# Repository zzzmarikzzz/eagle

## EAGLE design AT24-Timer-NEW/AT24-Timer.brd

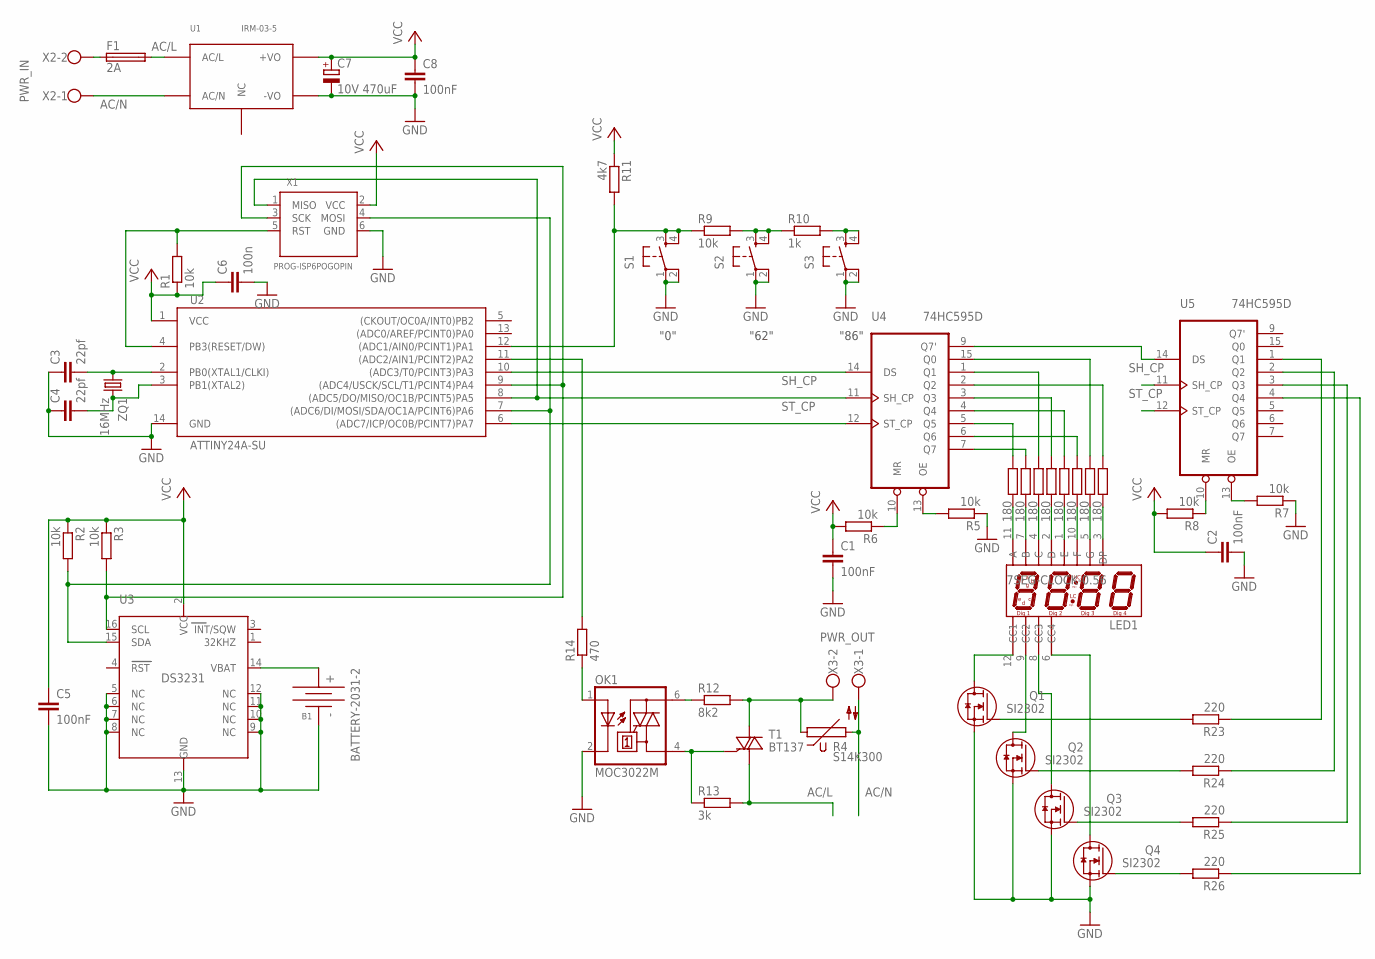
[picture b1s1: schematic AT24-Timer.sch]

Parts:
B1: BATTERY-2031-2; BTH2032-2
C1, C2, C5: 100nF; C0603
C3, C4: 22pf; C0603
C6: 100n; C0603
C7: 10V 470uF; D/7343-31W
C8: 100nF; C0805
F1: 2A; SH22,5A
LED1: 7SEG-CLOCK-0.56; 7SEG_4DIG_0.56
OK1: MOC3022M; DIL06
Q1, Q2, Q3, Q4: SI2302; SOT-23-GSD
R1, R2, R3, R5, R6, R7, R8, R9: 10k; R0805
R4: S14K300
R10: 1k; R0805
R11: 4k7; R0805
R12: 8k2; 0207/7
R13: 3k; 0207/7
R14: 470; R0805
R15, R16, R17, R18, R19, R20, R21, R22: 180; R0805
R23, R24, R25, R26: 220; R0805
S1, S2, S3: DTS-6
T1: BT137; TO220AB
U1: IRM-03-5; IRM-03-*
U2: ATTINY24A-SU; SO14
U3: DS3231; SO16L
U4, U5: 74HC595D; SO16
X1: PROG-ISP6POGOPIN; PROG_POGOPIN
X2: PWR_IN; W237-102
X3: PWR_OUT; W237-102
ZQ1: 16MHz; HC49/S

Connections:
AC/L: F1.2, R13.2, T1.1 (A1), U1.P$1 (AC/L)
AC/N: R4.2, U1.P$2 (AC/N), X2.1, X3.1
GND: B1.-, C1.2, C2.2, C3.1, C4.1, C5.2, C6.2, C7.-, C8.2, OK1.2 (C), Q1.S, Q2.S, Q3.S, Q4.S, R5.1, R7.1, S1.1, S1.2, S2.1, S2.2, S3.1, S3.2, U1.P$4 (-VO), U2.14 (GND), U3.5 (NC), U3.6 (NC), U3.7 (NC), U3.8 (NC), U3.9 (NC), U3.10 (NC), U3.11 (NC), U3.12 (NC), U3.13 (GND), U4.8 (GND), U5.8 (GND), X1.6 (GND)
unnamed: B1.+, U3.14 (VBAT)
unnamed: F1.1, X2.2
unnamed: R2.2, U2.7 ((ADC6/DI/MOSI/SDA/OC1A/PCINT6)PA6), U3.15 (SDA), X1.4 (MOSI)
unnamed: R3.2, U2.9 ((ADC4/USCK/SCL/T1/PCINT4)PA4), U3.16 (SCL), X1.3 (SCK)
unnamed: R1.2, U2.4 (PB3(RESET/DW)), X1.5 (RST)
unnamed: R9.2, R10.1, S2.3, S2.4
unnamed: C3.2, U2.2 (PB0(XTAL1/CLKI)), ZQ1.1
unnamed: C4.2, U2.3 (PB1(XTAL2)), ZQ1.2
unnamed: R6.1, U4.10 (MR)
unnamed: R9.1, R11.2, S1.3, S1.4, U2.12 ((ADC1/AIN0/PCINT1)PA1)
unnamed: OK1.6 (A2), R12.1
unnamed: R4.1, R12.2, T1.2 (A2), X3.2
unnamed: OK1.4 (A1), R13.1, T1.3 (G)
unnamed: R5.2, U4.13 (OE)
unnamed: OK1.1 (A), R14.1
unnamed: R8.1, U5.10 (MR)
unnamed: R7.2, U5.13 (OE)
unnamed: U2.10 ((ADC3/T0/PCINT3)PA3), U4.14 (DS)
unnamed: R15.1, U4.5 (Q5)
unnamed: R16.1, U4.7 (Q7)
unnamed: U4.9 (Q7'), U5.14 (DS)
unnamed: R17.1, U4.1 (Q1)
unnamed: R18.1, U4.3 (Q3)
unnamed: R19.1, U4.4 (Q4)
unnamed: R20.1, U4.6 (Q6)
unnamed: R21.1, U4.15 (Q0)
unnamed: R22.1, U4.2 (Q2)
unnamed: LED1.12 (CC1), Q1.D
unnamed: LED1.9 (CC2), Q2.D
unnamed: LED1.8 (CC3), Q3.D
unnamed: LED1.6 (CC4), Q4.D
unnamed: R23.1, U5.1 (Q1)
unnamed: R24.1, U5.2 (Q2)
unnamed: R25.1, U5.3 (Q3)
unnamed: R26.1, U5.4 (Q4)
unnamed: R10.2, S3.3, S3.4
unnamed: LED1.7 (B), R16.2
unnamed: LED1.4 (C), R17.2
unnamed: LED1.2 (D), R18.2
unnamed: LED1.1 (E), R19.2
unnamed: LED1.10 (F), R20.2
unnamed: LED1.5 (G), R21.2
unnamed: LED1.3 (DP), R22.2
unnamed: LED1.11 (A), R15.2
unnamed: Q4.G, R26.2
unnamed: Q3.G, R25.2
unnamed: Q2.G, R24.2
unnamed: Q1.G, R23.2
NC: U1.P$3 (NC)
OPTOCOUP: R14.2, U2.11 ((ADC2/AIN1/PCINT2)PA2)
SH_CP: U2.8 ((ADC5/DO/MISO/OC1B/PCINT5)PA5), U4.11 (SH_CP), U5.11 (SH_CP), X1.1 (MISO)
ST_CP: U2.6 ((ADC7/ICP/OC0B/PCINT7)PA7), U4.12 (ST_CP), U5.12 (ST_CP)
VCC: C1.1, C2.1, C5.1, C6.1, C7.+, C8.1, R1.1, R2.1, R3.1, R6.2, R8.2, R11.1, U1.P$5 (+VO), U2.1 (VCC), U3.2 (VCC), U4.16 (VCC), U5.16 (VCC), X1.2 (VCC)

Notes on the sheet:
"0"
"62"
"86"

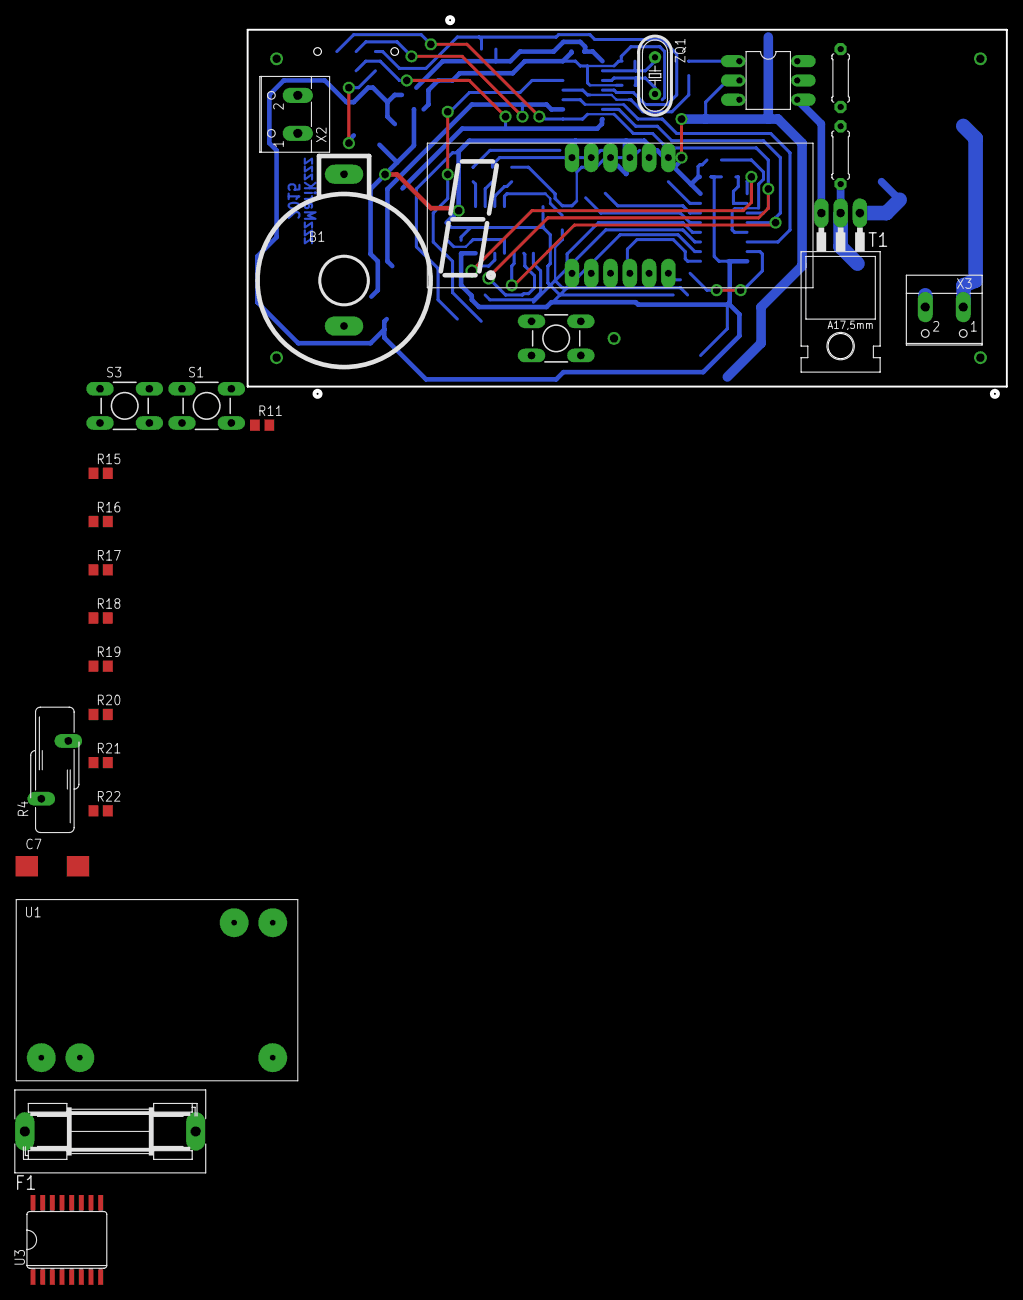
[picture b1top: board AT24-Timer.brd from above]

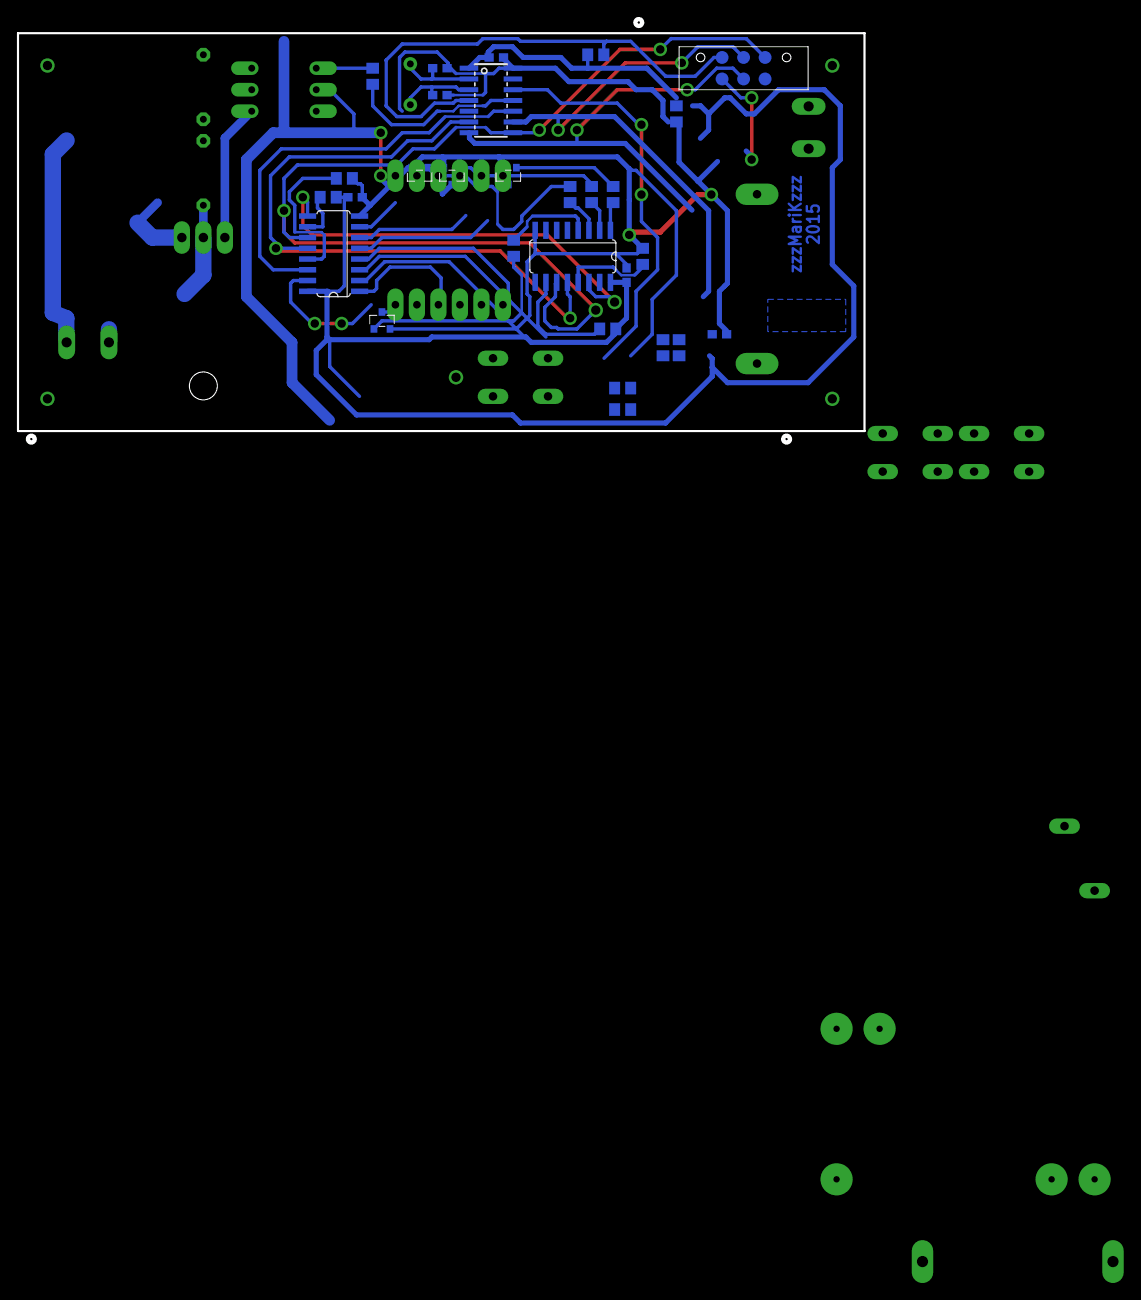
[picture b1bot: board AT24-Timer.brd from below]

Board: 2 copper layers, 100.0 x 49.7 mm, 55 parts (29 on the bottom side), 55 nets.

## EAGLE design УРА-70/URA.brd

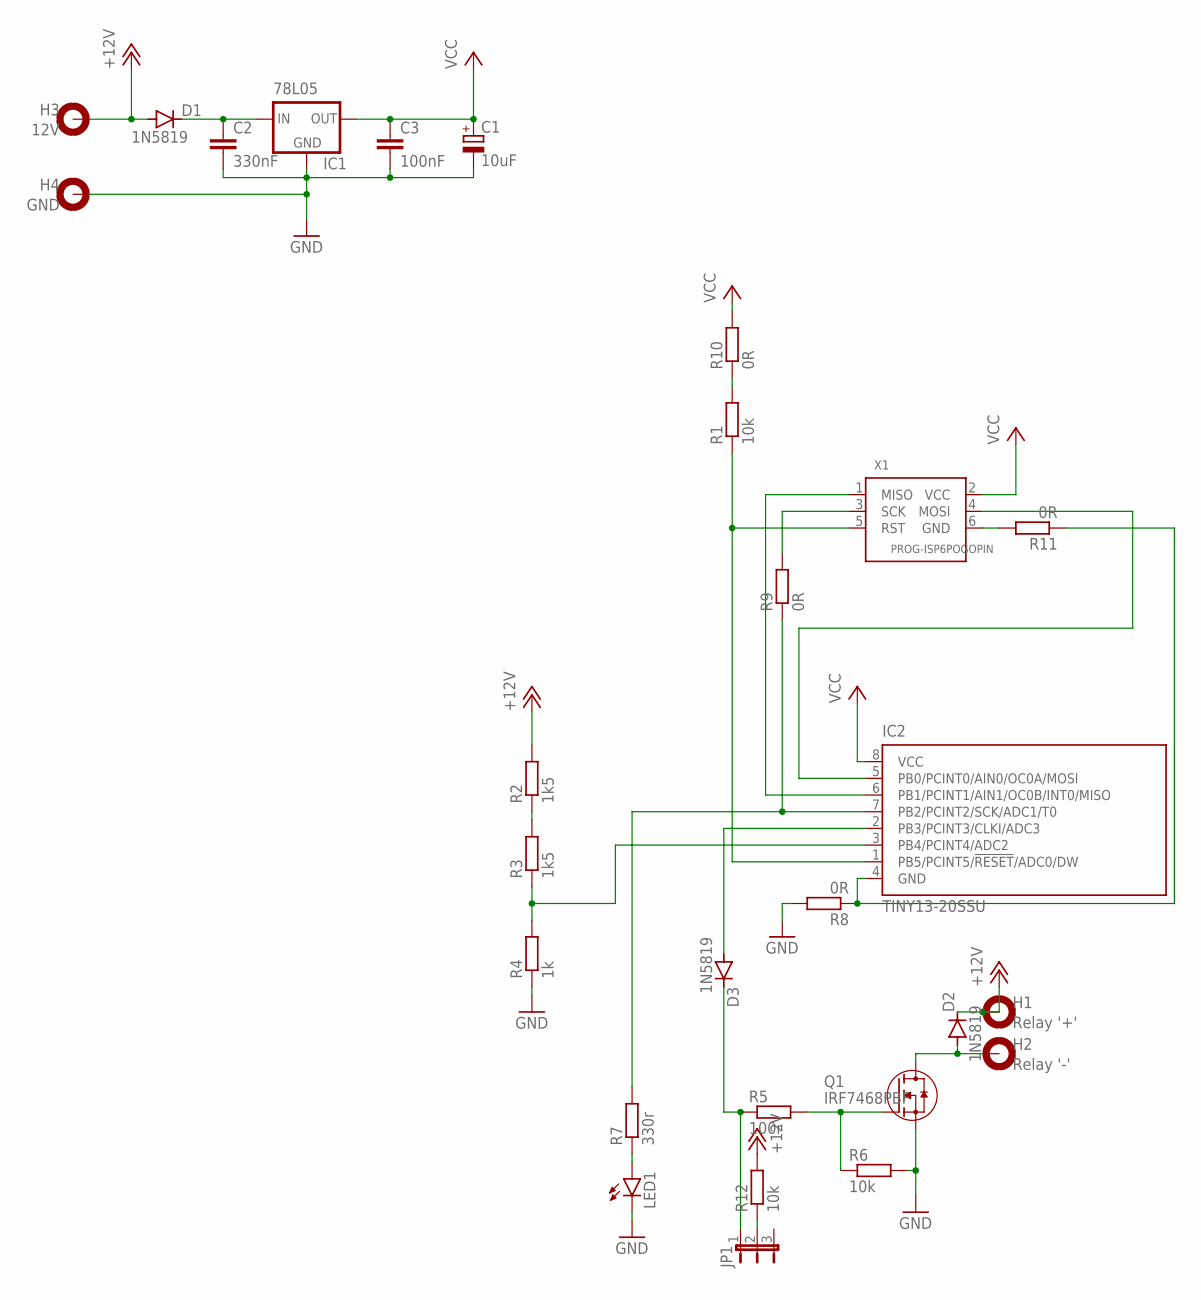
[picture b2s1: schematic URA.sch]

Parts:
C1: 10uF; CT3216
C2: 330nF; C0805K
C3: 100nF; C0805K
D1, D2, D3: 1N5819; SOD-123_MINI-SMA
H1: Relay '+'; 2,8-PAD
H2: Relay '-'; 2,8-PAD
H3: 12V; 2,8-PAD
H4: GND; 2,8-PAD
IC1: 78L05; 78LXX-SOT89
IC2: TINY13-20SSU; 8S1
JP1: JP2E; JP2
LED1: LEDCHIP-LED0805; CHIP-LED0805
Q1: IRF7468PBF; SO08
R1, R6, R12: 10k; R0805
R2, R3: 1k5; R0805
R4: 1k; R0805
R5: 100r; R0805
R7: 330r; R0805
R8, R9, R10, R11: 0R; R1206
X1: PROG-ISP6POGOPIN; PROG_POGOPIN

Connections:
+12V: D1.A, D2.C, H1.B2,8, H3.B2,8, R2.2, R12.2
GND: C1.-, C2.2, C3.2, H4.B2,8, IC1.GND@0 (GND), IC1.GND@1 (GND), LED1.C, Q1.1 (S), Q1.2 (S), Q1.3 (S), R4.1, R6.2, R8.2
unnamed: IC2.6 (PB1/PCINT1/AIN1/OC0B/INT0/MISO), X1.1 (MISO)
unnamed: IC2.5 (PB0/PCINT0/AIN0/OC0A/MOSI), X1.4 (MOSI)
unnamed: IC2.1 (PB5/PCINT5/!RESET!/ADC0/DW), R1.1, X1.5 (RST)
unnamed: C2.1, D1.C, IC1.IN
unnamed: IC2.7 (PB2/PCINT2/SCK/ADC1/T0), R7.2, R9.1
unnamed: R2.1, R3.2
unnamed: IC2.3 (PB4/PCINT4/ADC2), R3.1, R4.2
unnamed: Q1.4 (G), R5.2, R6.1
unnamed: D3.A, IC2.2 (PB3/PCINT3/CLKI/ADC3)
unnamed: D2.A, H2.B2,8, Q1.5 (D), Q1.6 (D), Q1.7 (D), Q1.8 (D)
unnamed: LED1.A, R7.1
unnamed: D3.C, JP1.1, R5.1
unnamed: R9.2, X1.3 (SCK)
unnamed: R1.2, R10.1
unnamed: R11.2, X1.6 (GND)
unnamed: IC2.4 (GND), R8.1, R11.1
unnamed: JP1.2, R12.1
VCC: C1.+, C3.1, IC1.OUT, IC2.8 (VCC), R10.2, X1.2 (VCC)

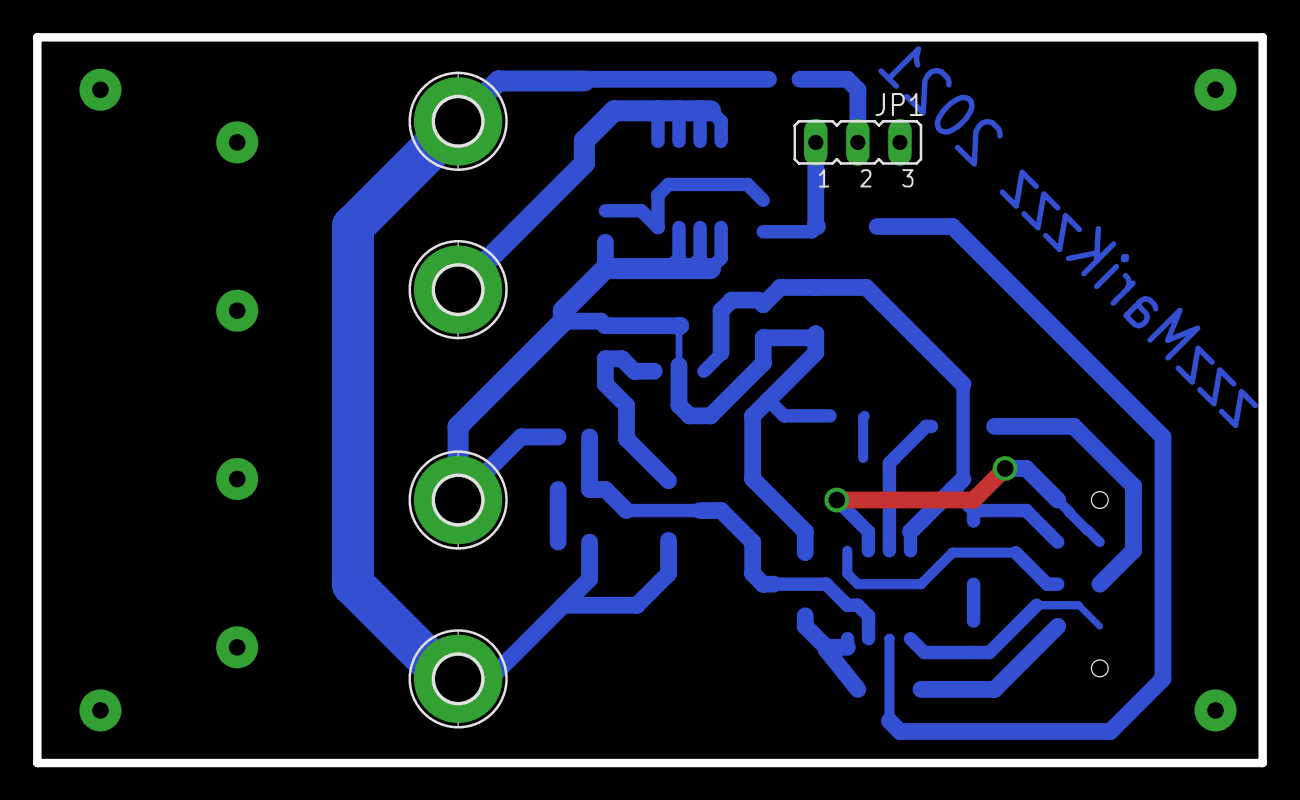
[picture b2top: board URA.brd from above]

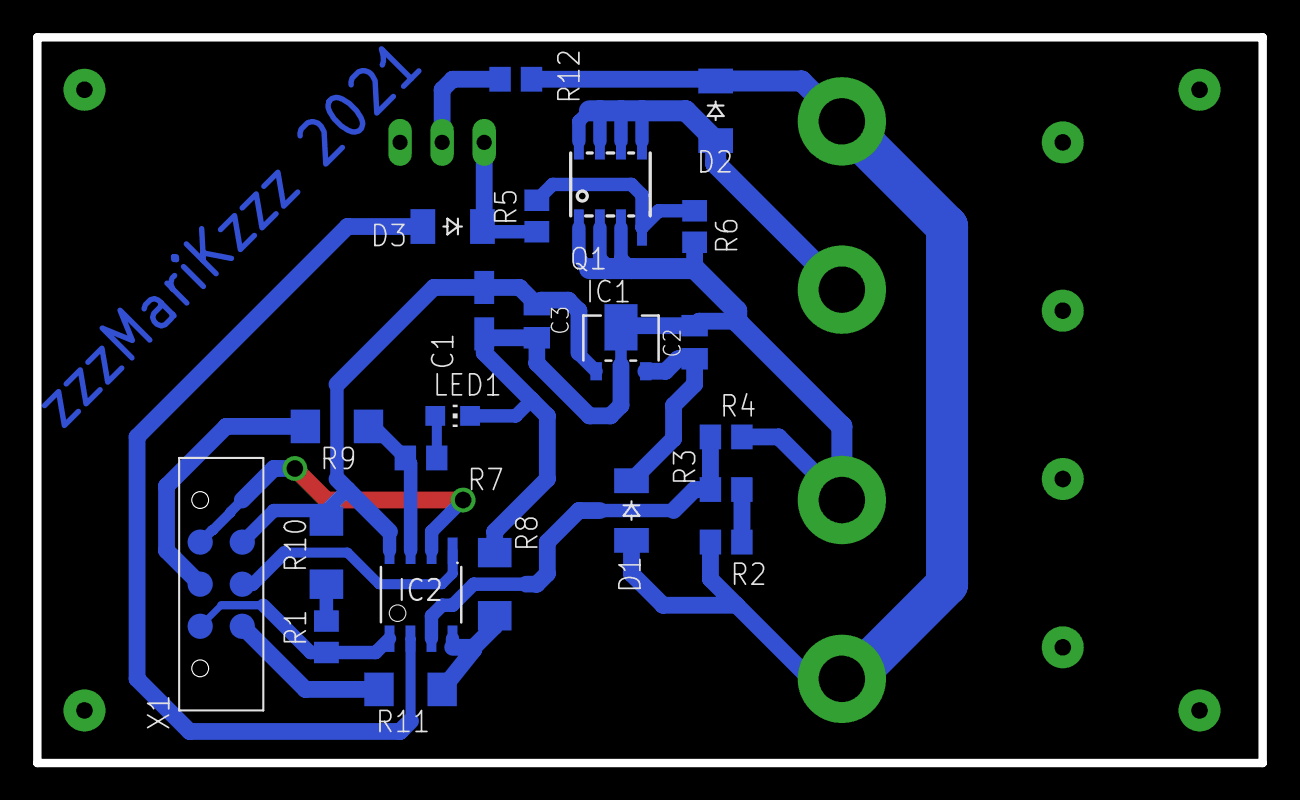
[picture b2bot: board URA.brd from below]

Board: 2 copper layers, 74.0 x 43.8 mm, 28 parts (23 on the bottom side), 20 nets.

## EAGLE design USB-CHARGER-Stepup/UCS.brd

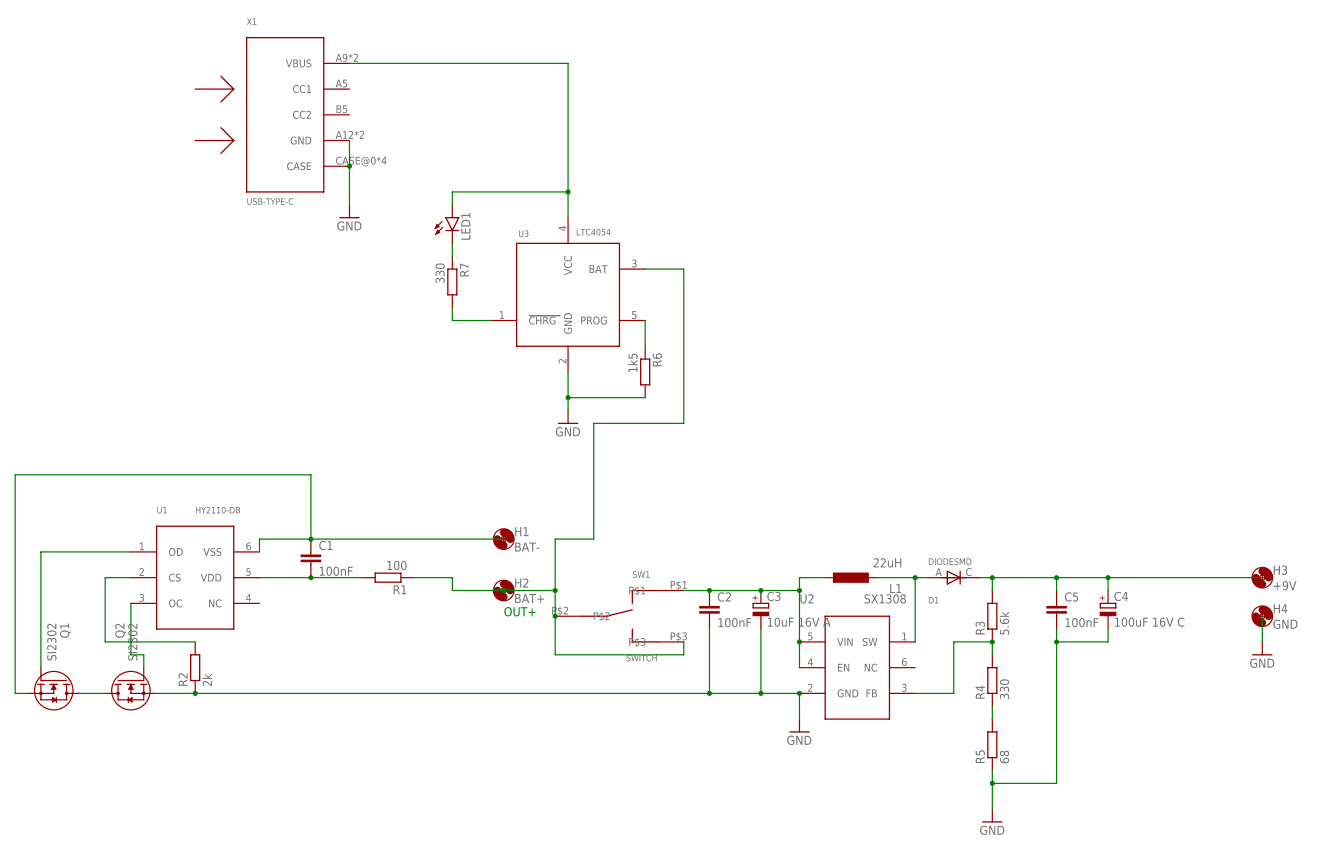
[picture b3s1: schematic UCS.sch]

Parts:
C1, C2, C5: 100nF; C0805
C3: 10uF 16V A; SMC_A
C4: 100uF 16V C; SMC_C
D1: DIODESMD; DO214AC
H1: BAT-; 3,0
H2: BAT+; 3,0
H3: +9V; 3,0
H4: GND; 3,0
L1: 22uH; L7*7*5
LED1: LEDCHIPLED_0603; CHIPLED_0603
Q1, Q2: SI2302; SOT-23-GSD
R1: 100; R0805
R2: 2k; R0805
R3: 5.6k; R0805
R4, R7: 330; R0805
R5: 68; R0805
R6: 1k5; R0805
SW1: SWITCH
U1: HY2110-DB; SOT-23-6
U2: SX1308; SOT-23-6
U3: LTC4054; SOT-23-5
X1: USB-TYPE-C

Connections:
GND: C2.2, C3.-, C4.-, C5.2, H4.P$1, Q2.S, R2.1, R5.1, R6.2, U2.2 (GND), U3.2 (GND), X1.A12 (GND), X1.B12 (GND), X1.CASE@0 (CASE), X1.CASE@1 (CASE), X1.CASE@2 (CASE), X1.CASE@3 (CASE)
unnamed: H2.P$1, R1.1, SW1.P$2, SW1.P$3, U3.3 (BAT)
unnamed: C1.2, R1.2, U1.5 (VDD)
unnamed: C1.1, H1.P$1, Q1.S, U1.6 (VSS)
unnamed: Q1.D, Q2.D
unnamed: D1.A (ANOD), L1.P$2 (2), U2.1 (SW)
unnamed: Q1.G, U1.1 (OD)
unnamed: Q2.G, U1.3 (OC)
unnamed: R2.2, U1.2 (CS)
unnamed: C4.+, C5.1, D1.C (KATOD), H3.P$1, R3.2
unnamed: R3.1, R4.2, U2.3 (FB)
unnamed: R4.1, R5.2
unnamed: LED1.A, U3.4 (VCC), X1.A9 (VBUS), X1.B9 (VBUS)
unnamed: LED1.C, R7.1
unnamed: R7.2, U3.1 (CHRG)
unnamed: R6.1, U3.5 (PROG)
unnamed: C2.1, C3.+, L1.P$1 (1), SW1.P$1, U2.4 (EN), U2.5 (VIN)

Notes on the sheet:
OUT+

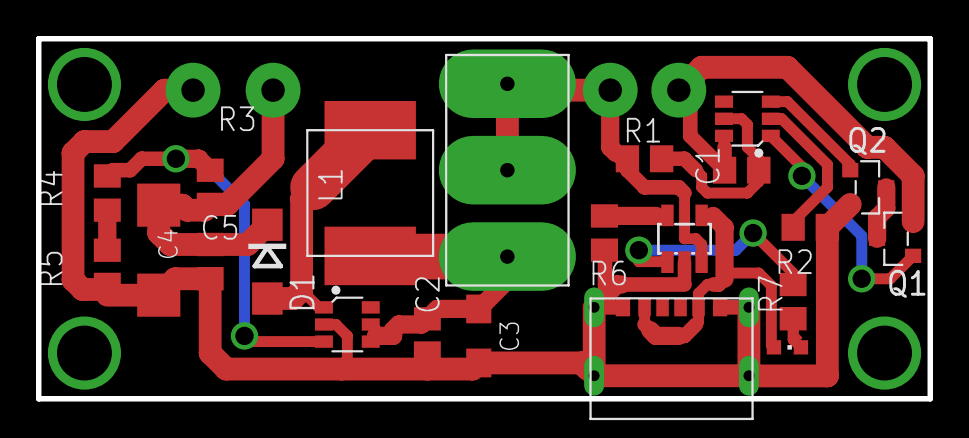
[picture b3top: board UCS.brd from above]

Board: 2 copper layers, 49.5 x 20.0 mm, 26 parts (1 on the bottom side), 17 nets.

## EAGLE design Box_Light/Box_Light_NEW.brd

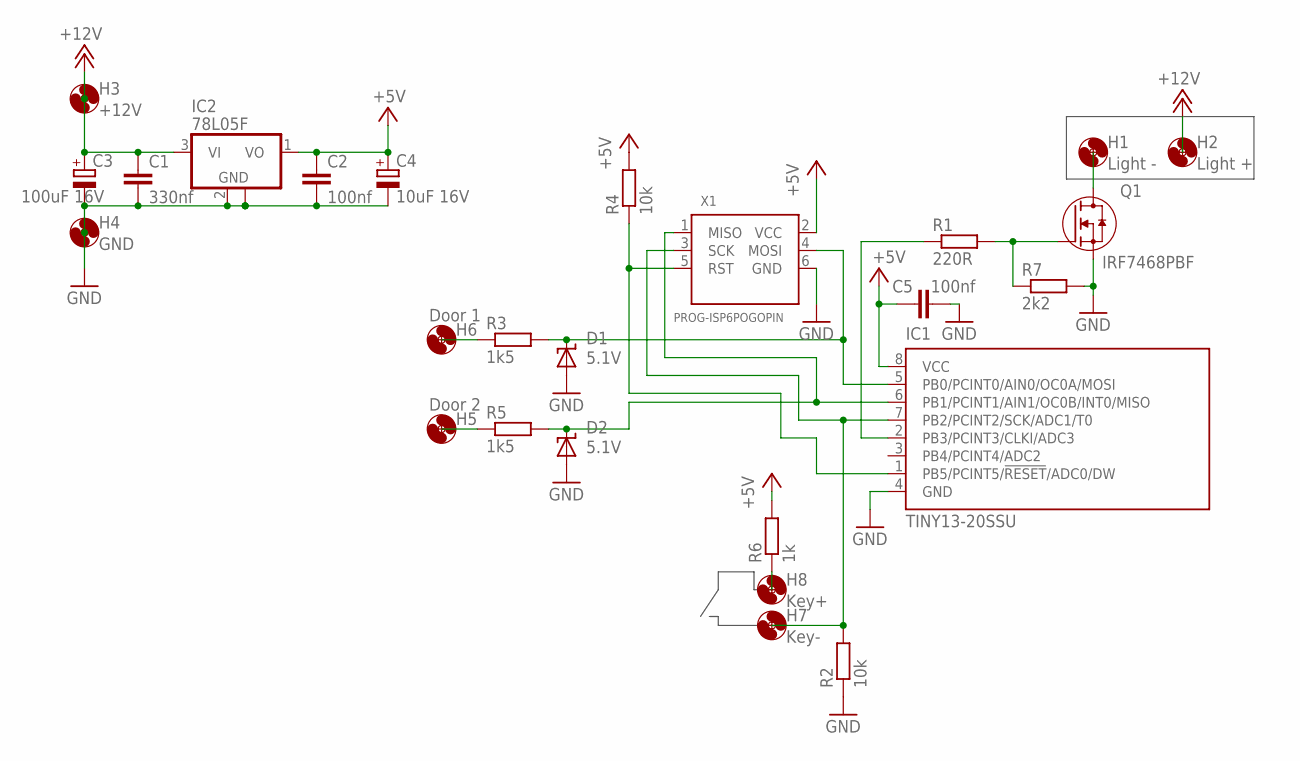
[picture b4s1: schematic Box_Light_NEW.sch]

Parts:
C1: 330nf; C0805
C2, C5: 100nf; C0805
C3: 100uF 16V; SMC_C
C4: 10uF 16V; SMC_B
D1, D2: 5.1V; SOD123
H1: Light -; 3,0
H2: Light +; 3,0
H3: +12V; 3,0
H4: GND; 3,0
H5: Door 2; 2,8
H6: Door 1; 2,8
H7: Key-; 2,8
H8: Key+; 2,8
IC1: TINY13-20SSU; 8S1
IC2: 78L05F; SOT89
Q1: IRF7468PBF; SO08
R1: 220R; R0805
R2, R4: 10k; R0805
R3, R5: 1k5; R0805
R6: 1k; R0805
R7: 2k2; R0805
X1: PROG-ISP6POGOPIN; PROG_POGOPIN

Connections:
+5V: C2.1, C4.+, C5.1, IC1.8 (VCC), IC2.1 (VO), R4.2, R6.2, X1.2 (VCC)
+12V: C1.1, C3.+, H2.P$1, H3.P$1, IC2.3 (VI)
GND: C1.2, C2.2, C3.-, C4.-, C5.2, D1.A, D2.A, H4.P$1, IC1.4 (GND), IC2.2 (GND), IC2.2@1 (GND), Q1.1 (S), Q1.2 (S), Q1.3 (S), R2.1, R7.2, X1.6 (GND)
unnamed: Q1.4 (G), R1.2, R7.1
unnamed: H1.P$1, Q1.5 (D), Q1.6 (D), Q1.7 (D), Q1.8 (D)
unnamed: H7.P$1, IC1.7 (PB2/PCINT2/SCK/ADC1/T0), R2.2, X1.3 (SCK)
unnamed: H5.P$1, R5.1
unnamed: D1.C, IC1.5 (PB0/PCINT0/AIN0/OC0A/MOSI), R3.2, X1.4 (MOSI)
unnamed: IC1.2 (PB3/PCINT3/CLKI/ADC3), R1.1
unnamed: IC1.1 (PB5/PCINT5/!RESET!/ADC0/DW), R4.1, X1.5 (RST)
unnamed: D2.C, IC1.6 (PB1/PCINT1/AIN1/OC0B/INT0/MISO), R5.2, X1.1 (MISO)
unnamed: H8.P$1, R6.1
unnamed: H6.P$1, R3.1

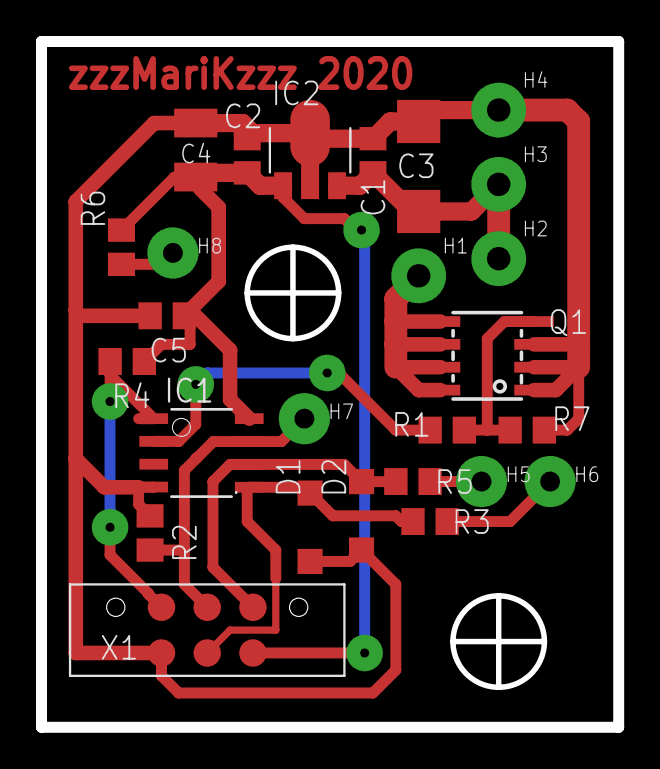
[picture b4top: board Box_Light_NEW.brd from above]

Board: 2 copper layers, 32.1 x 38.1 mm, 26 parts (0 on the bottom side), 13 nets.

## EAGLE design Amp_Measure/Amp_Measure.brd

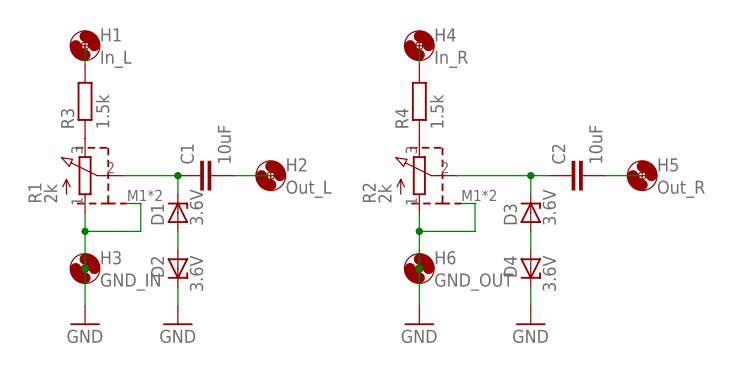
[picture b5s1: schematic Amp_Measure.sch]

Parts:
C1, C2: 10uF; C0805K
D1, D2, D3, D4: 3.6V; SOD80C
H1: In_L; 3,3
H2: Out_L; 3,3
H3: GND_IN; 3,3
H4: In_R; 3,3
H5: Out_R; 3,3
H6: GND_OUT; 3,3
R1, R2: 2k; POTENT
R3, R4: 1.5k; R0805W

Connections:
GND: D2.C, D4.C, H3.P$1, H6.P$1, R1.1 (A), R1.M1 (CASE), R1.M2 (CASE), R2.1 (A), R2.M1 (CASE), R2.M2 (CASE)
unnamed: R1.3 (E), R3.1
unnamed: R2.3 (E), R4.1
unnamed: H1.P$1, R3.2
unnamed: C1.1, D1.C, R1.2 (S)
unnamed: D1.A, D2.A
unnamed: C1.2, H2.P$1
unnamed: D3.A, D4.A
unnamed: H4.P$1, R4.2
unnamed: C2.1, D3.C, R2.2 (S)
unnamed: C2.2, H5.P$1

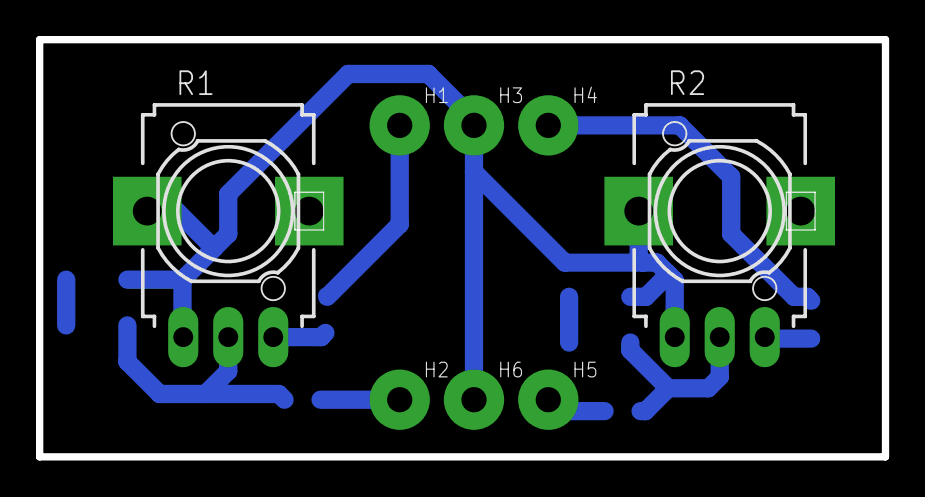
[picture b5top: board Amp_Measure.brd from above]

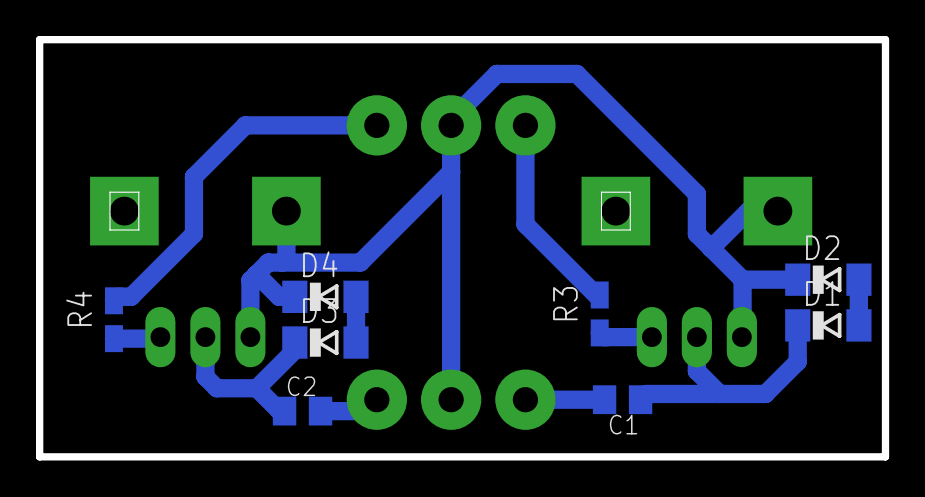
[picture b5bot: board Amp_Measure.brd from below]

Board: 2 copper layers, 47.0 x 23.2 mm, 16 parts (8 on the bottom side), 11 nets.

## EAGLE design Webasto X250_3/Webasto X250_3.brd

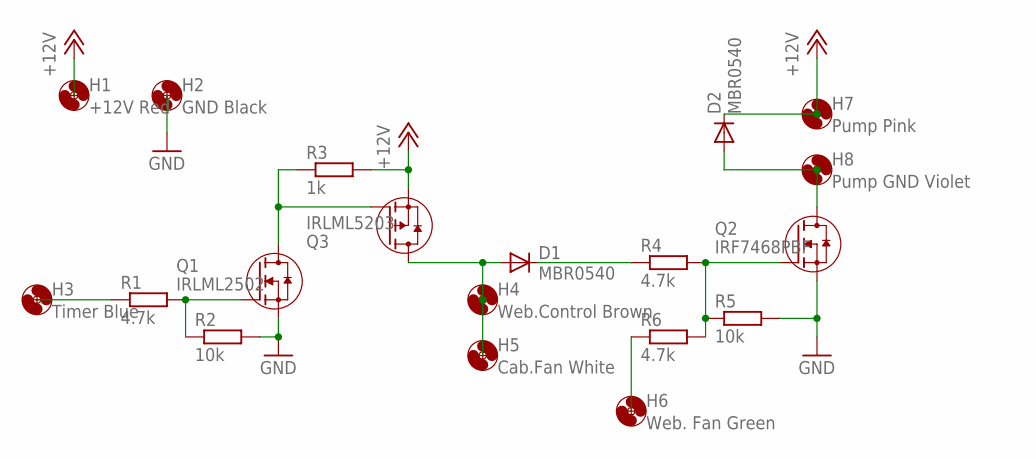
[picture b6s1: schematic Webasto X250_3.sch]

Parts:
D1, D2: MBR0540; SOD-123_MINI-SMA
H1: +12V Red; 3,6
H2: GND Black; 3,6
H3: Timer Blue; 3,6
H4: Web.Control Brown; 3,6
H5: Cab.Fan White; 3,6
H6: Web. Fan Green; 3,6
H7: Pump Pink; 3,6
H8: Pump GND Violet; 3,6
Q1: IRLML2502; SOT-23-GSD
Q2: IRF7468PBF; SO08
Q3: IRLML5203; SOT-23-GSD
R1, R4, R6: 4.7k; R0603
R2, R5: 10k; R0603
R3: 1k; R0603

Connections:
+12V: D2.C, H1.P$1, H7.P$1, Q3.S, R3.2
GND: H2.P$1, Q1.S, Q2.1 (S), Q2.2 (S), Q2.3 (S), R2.2, R5.2
unnamed: Q1.G, R1.2, R2.1
unnamed: H3.P$1, R1.1
unnamed: Q1.D, Q3.G, R3.1
unnamed: D1.A, H4.P$1, H5.P$1, Q3.D
unnamed: Q2.4 (G), R4.2, R5.1, R6.2
unnamed: D2.A, H8.P$1, Q2.5 (D), Q2.6 (D), Q2.7 (D), Q2.8 (D)
unnamed: H6.P$1, R6.1
unnamed: D1.C, R4.1

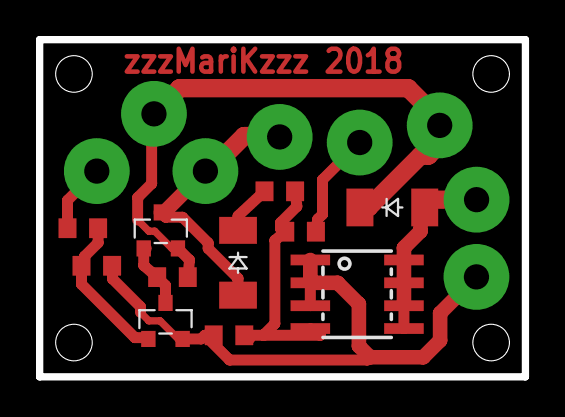
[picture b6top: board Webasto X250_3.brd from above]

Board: 2 copper layers, 27.0 x 18.7 mm, 19 parts (0 on the bottom side), 10 nets.

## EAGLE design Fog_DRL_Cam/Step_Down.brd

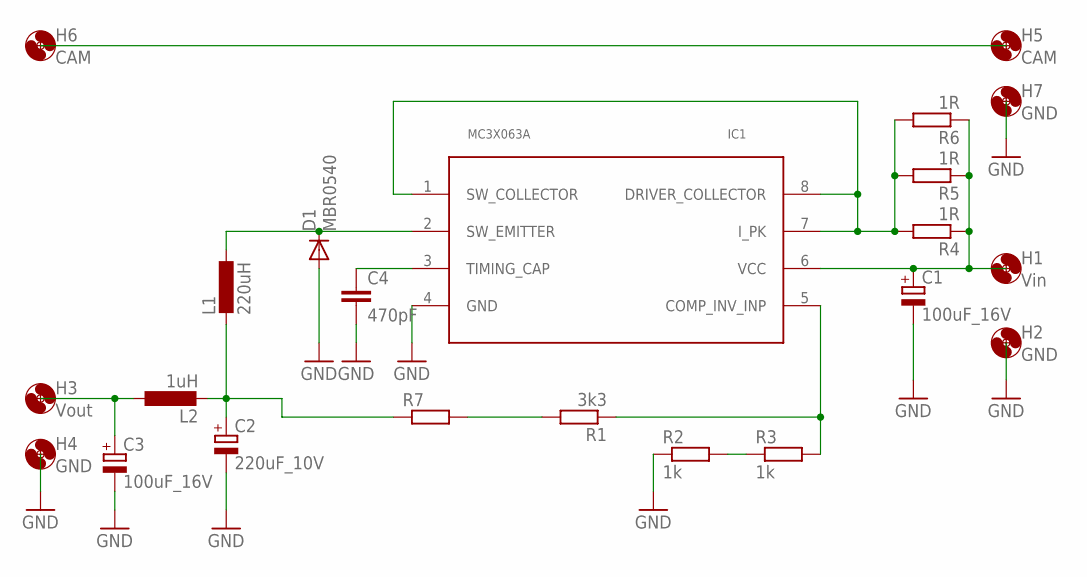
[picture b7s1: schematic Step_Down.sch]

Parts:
C1, C3: 100uF_16V; D/7343-31W
C2: 220uF_10V; D/7343-31W
C4: 470pF; C0805K
D1: MBR0540; SOD-123_MINI-SMA
H1: Vin; 2,8
H2, H4, H7: GND; 2,8
H3: Vout; 2,8
H5, H6: CAM; 2,8
IC1: MC3X063A; SO08
L1: 220uH; 2220
L2: 1uH; L1812
R1: 3k3; R0805
R2, R3: 1k; R0805
R4, R5, R6: 1R; R0805
R7: R-EU_R1206W; R1206W

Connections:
GND: C1.-, C2.-, C3.-, C4.2, D1.A, H2.P$1, H4.P$1, H7.P$1, IC1.4 (GND), R2.1
unnamed: R2.2, R3.1
unnamed: IC1.1 (SW_COLLECTOR), IC1.7 (I_PK), IC1.8 (DRIVER_COLLECTOR), R4.2, R5.2, R6.2
unnamed: C1.+, H1.P$1, IC1.6 (VCC), R4.1, R5.1, R6.1
unnamed: D1.C, IC1.2 (SW_EMITTER), L1.1
unnamed: C4.1, IC1.3 (TIMING_CAP)
unnamed: C2.+, L1.2, L2.2, R7.1
unnamed: H5.P$1, H6.P$1
unnamed: IC1.5 (COMP_INV_INP), R1.1, R3.2
unnamed: C3.+, H3.P$1, L2.1
unnamed: R1.2, R7.2

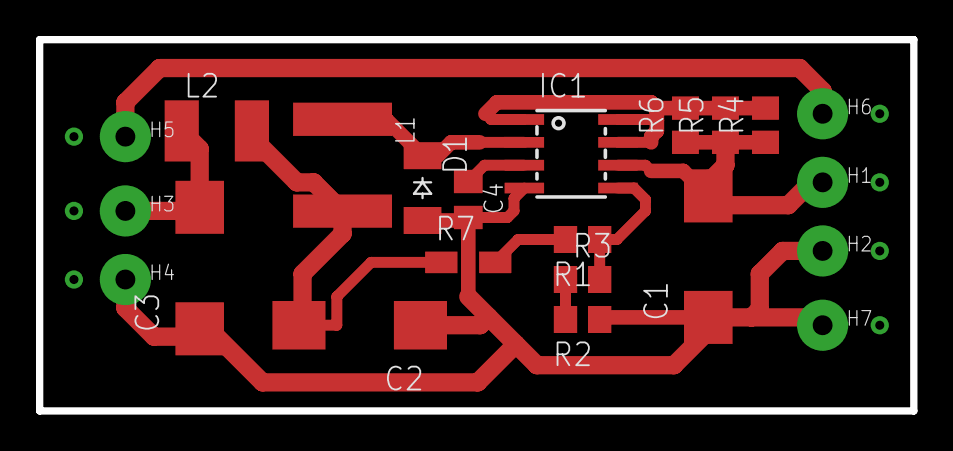
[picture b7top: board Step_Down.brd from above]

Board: 2 copper layers, 48.6 x 20.6 mm, 22 parts (0 on the bottom side), 11 nets.

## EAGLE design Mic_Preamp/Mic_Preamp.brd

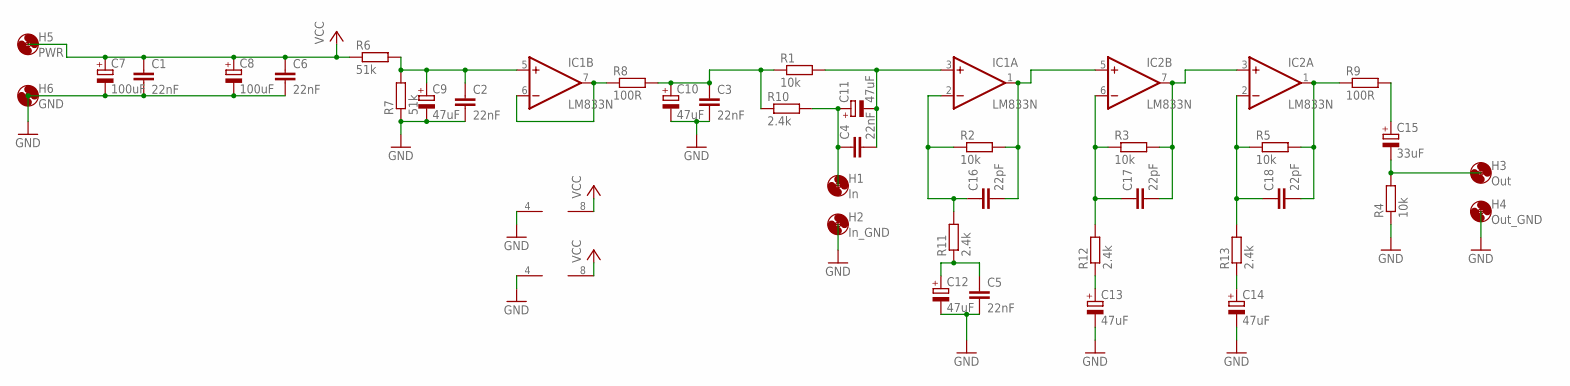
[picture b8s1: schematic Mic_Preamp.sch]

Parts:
C1, C2, C3, C4, C5, C6: 22nF; C050-025X075
C7, C8: 100uF; C/6032-28R
C9, C10, C11, C12, C13, C14: 47uF; E2,5-5
C15: 33uF; E2,5-5
C16, C17, C18: 22pF; C0603K
H1: In; 3,0
H2: In_GND; 3,0
H3: Out; 3,0
H4: Out_GND; 3,0
H5: PWR; 3,0
H6: GND; 3,0
IC1, IC2: LM833N; DIL08
R1, R2, R3, R4, R5: 10k; R0805
R6, R7: 51k; R0805
R8, R9: 100R; R0805
R10, R11, R12, R13: 2.4k; R0805

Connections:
GND: C1.2, C2.2, C3.2, C5.2, C6.2, C7.-, C8.-, C9.-, C10.-, C12.-, C13.-, C14.-, H2.P$1, H4.P$1, H6.P$1, IC1.4 (V-), IC2.4 (V-), R4.1, R7.1
unnamed: C2.1, C9.+, IC1.5 (+IN), R6.2, R7.2
unnamed: IC1.6 (-IN), IC1.7 (OUT), R8.1
unnamed: C3.1, C10.+, R1.1, R8.2, R10.1
unnamed: C4.2, C11.-, IC1.3 (+IN), R1.2
unnamed: C4.1, C11.+, H1.P$1, R10.2
unnamed: C16.2, IC1.1 (OUT), IC2.5 (+IN), R2.2
unnamed: C16.1, IC1.2 (-IN), R2.1, R11.2
unnamed: C5.1, C12.+, R11.1
unnamed: C17.1, IC2.6 (-IN), R3.1, R12.2
unnamed: C17.2, IC2.3 (+IN), IC2.7 (OUT), R3.2
unnamed: C13.+, R12.1
unnamed: C18.1, IC2.2 (-IN), R5.1, R13.2
unnamed: C18.2, IC2.1 (OUT), R5.2, R9.1
unnamed: C14.+, R13.1
unnamed: C15.+, R9.2
unnamed: C15.-, H3.P$1, R4.2
VCC: C1.1, C6.1, C7.+, C8.+, H5.P$1, IC1.8 (V+), IC2.8 (V+), R6.1

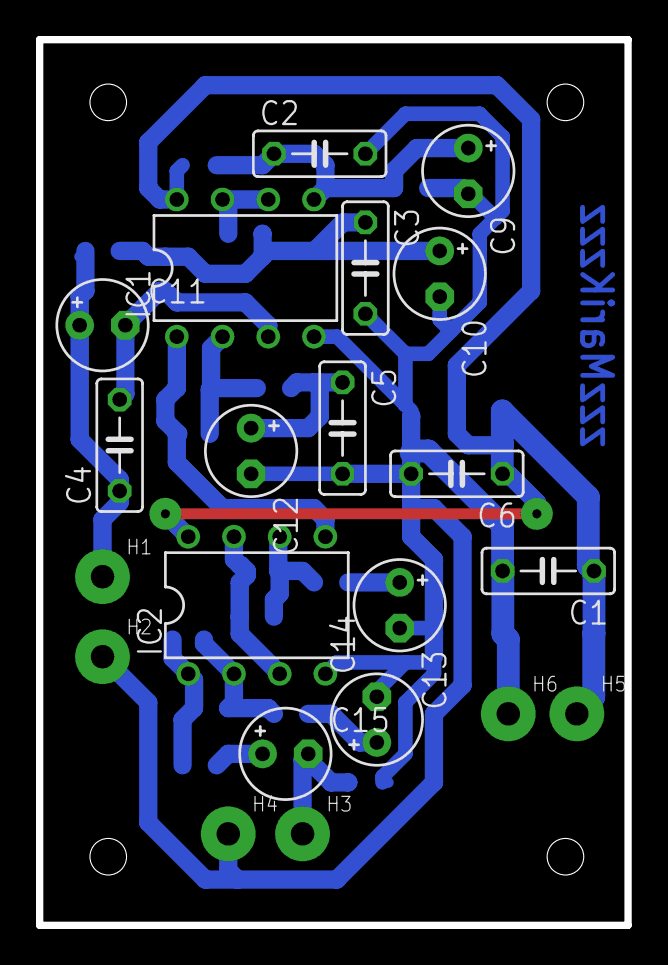
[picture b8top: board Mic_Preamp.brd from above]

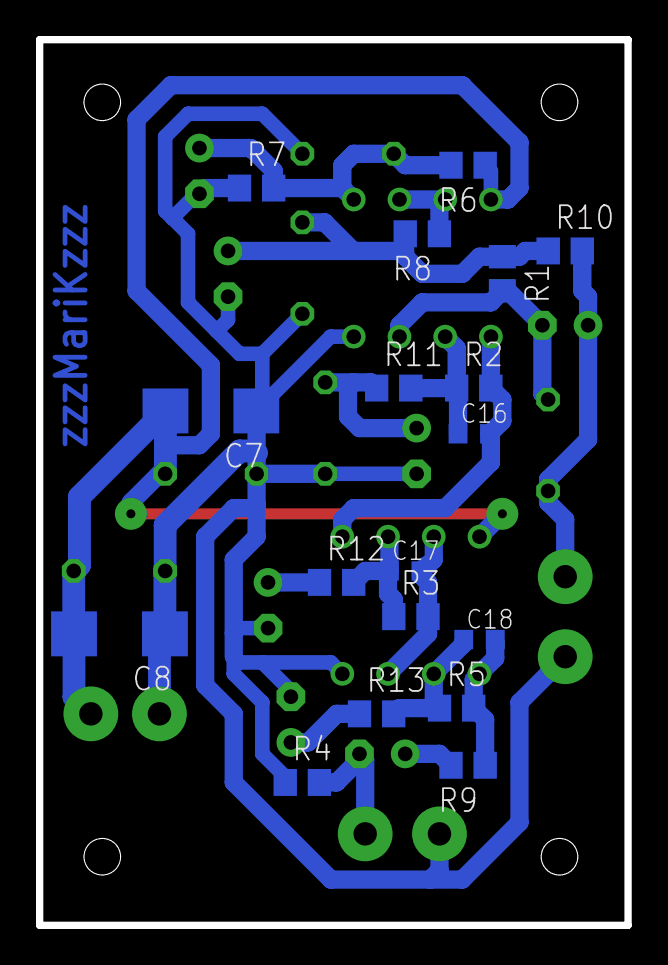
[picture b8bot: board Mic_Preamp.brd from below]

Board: 2 copper layers, 32.7 x 49.2 mm, 39 parts (18 on the bottom side), 18 nets.

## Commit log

2016-03-29 upload
2017-08-25 New Projects
2018-08-14 Добавлены ДХО работающие на ШИМ
2019-12-20 Новая версия света в будке и библиотека USB
2019-12-20 Новая версия CAM
2020-06-20 Check
2024-02-28 USB-Charger Stepup
